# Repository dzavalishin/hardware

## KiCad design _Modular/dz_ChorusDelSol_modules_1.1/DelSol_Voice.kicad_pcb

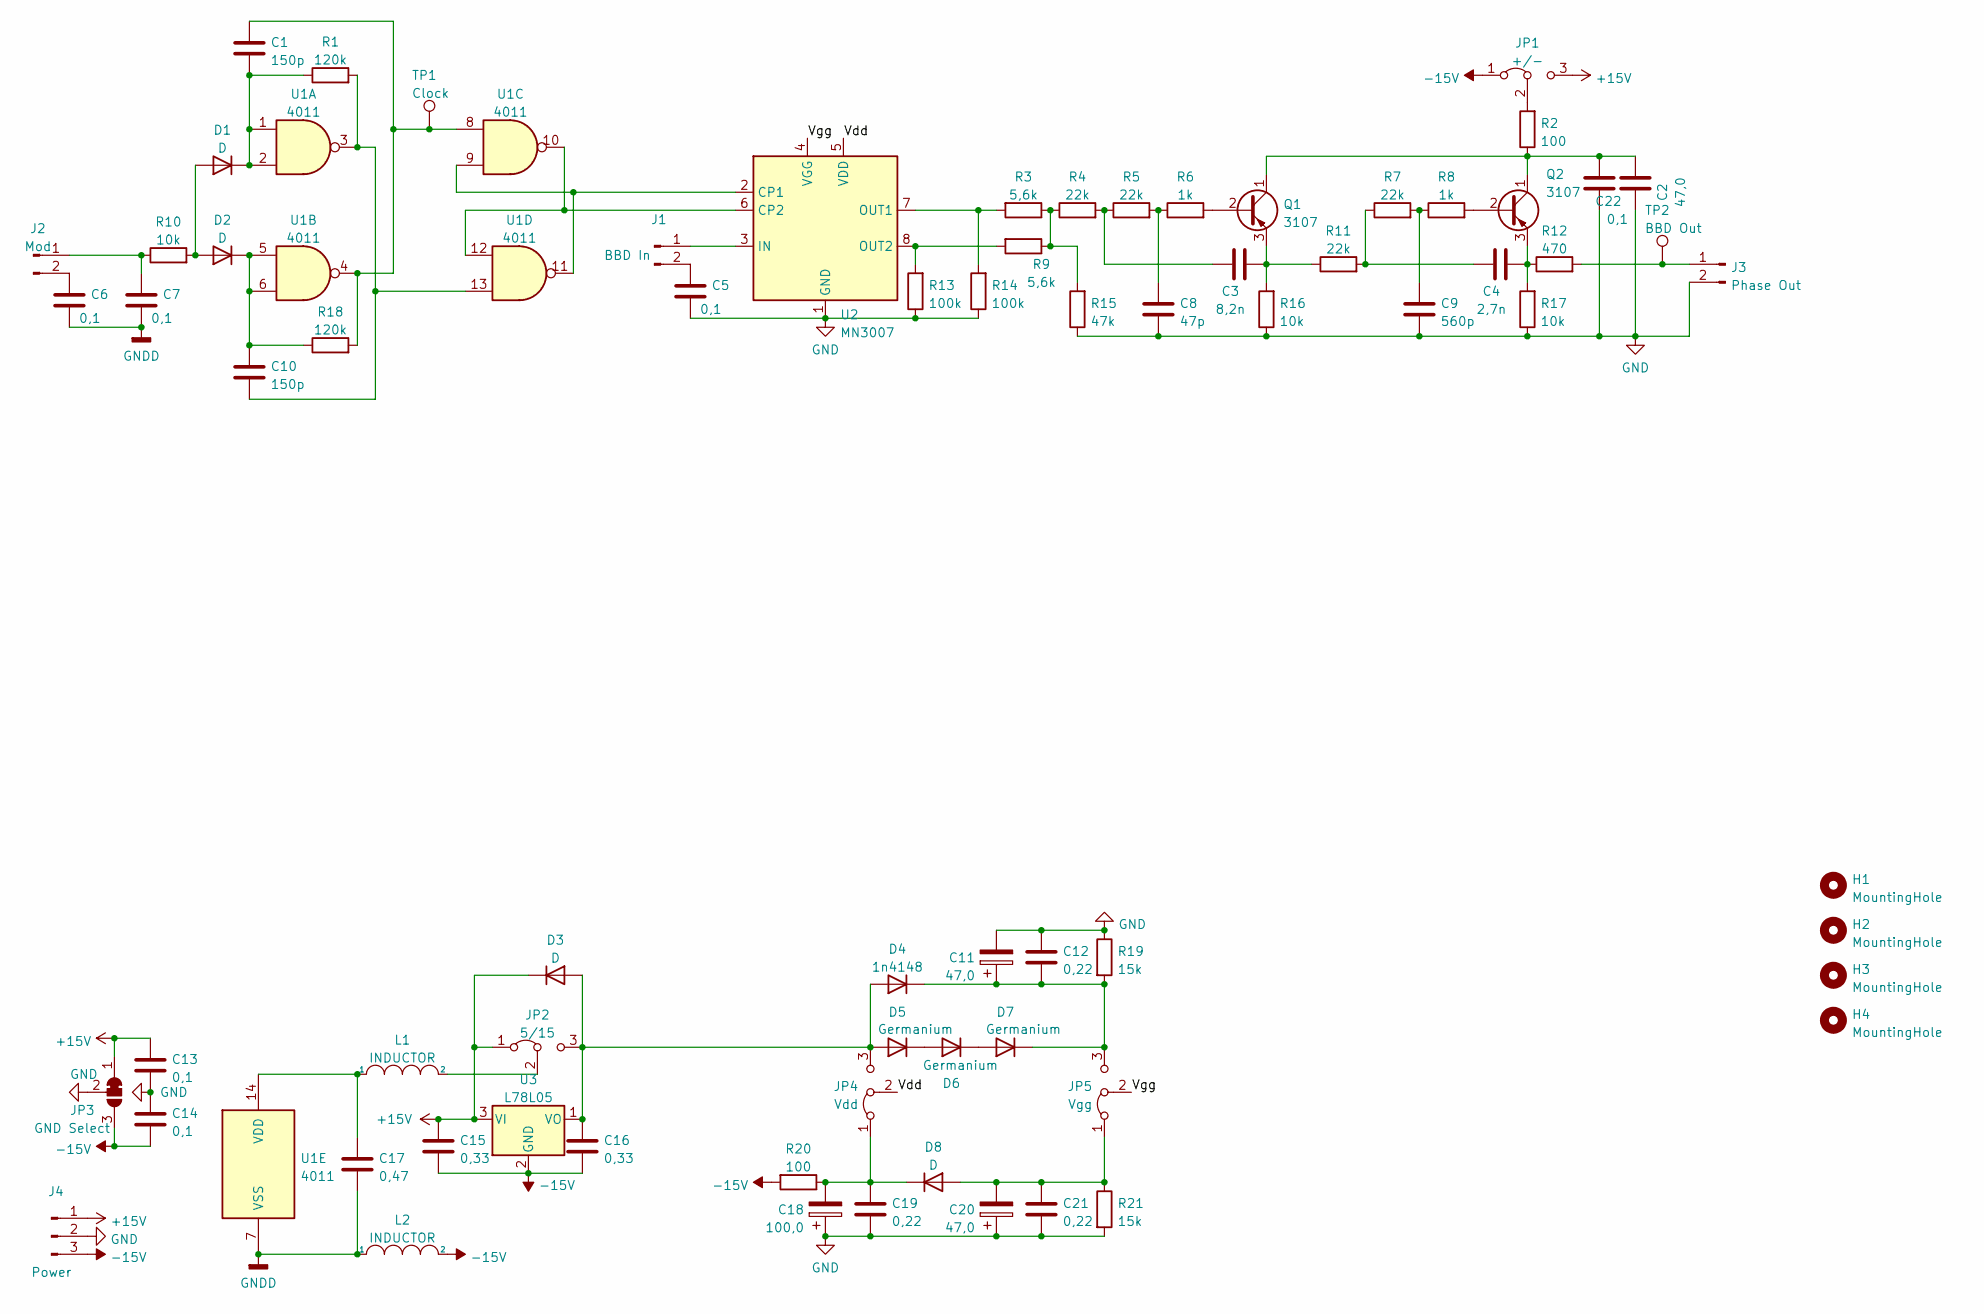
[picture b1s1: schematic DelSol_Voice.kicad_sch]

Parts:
C1, C10: 150p; C_Disc_D5.0mm_W2.5mm_P2.50mm
C2, C11, C20: 47,0; C_Elec_6.3x5.8
C3: 8,2n; C_Disc_D5.0mm_W2.5mm_P2.50mm
C4: 2,7n; C_Disc_D5.0mm_W2.5mm_P2.50mm
C5, C6, C7, C13, C14, C22: 0,1; C_1206_3216Metric_Pad1.33x1.80mm_HandSolder
C8: 47p; C_Disc_D5.0mm_W2.5mm_P2.50mm
C9: 560p; C_Disc_D5.0mm_W2.5mm_P2.50mm
C12, C19, C21: 0,22; C_0805_2012Metric_Pad1.18x1.45mm_HandSolder
C15, C16: 0,33; C_0805_2012Metric_Pad1.18x1.45mm_HandSolder
C17: 0,47; C_0805_2012Metric_Pad1.18x1.45mm_HandSolder
C18: 100,0; C_Elec_6.3x5.8
D1, D2, D3, D8: D; D_MiniMELF_Handsoldering
D4: 1n4148; D_MiniMELF_Handsoldering
D5, D6, D7: Germanium; D_5W_P12.70mm_Horizontal
H1, H2, H3, H4: MountingHole; MountingHole_3.2mm_M3
J1: BBD In; PinHeader_1x02_P2.54mm_Vertical
J2: Mod; PinHeader_1x02_P2.54mm_Vertical
J3: Phase Out; PinHeader_1x02_P2.54mm_Vertical
J4: Power; PinHeader_1x03_P2.54mm_Vertical
JP1: +/-; PinHeader_1x03_P2.54mm_Vertical
JP2: 5/15; PinHeader_1x03_P2.54mm_Vertical
JP3: GND Select; PinHeader_1x03_P2.54mm_Vertical
JP4: Vdd; PinHeader_1x03_P2.54mm_Vertical
JP5: Vgg; PinHeader_1x03_P2.54mm_Vertical
L1, L2: INDUCTOR; L_Radial_D10.0mm_P5.00mm_Fastron_07P
Q1, Q2: 3107; TO-92
R1, R18: 120k; R_1206_3216Metric_Pad1.30x1.75mm_HandSolder
R2, R20: 100; R_1206_3216Metric_Pad1.30x1.75mm_HandSolder
R3, R9: 5,6k; R_1206_3216Metric_Pad1.30x1.75mm_HandSolder
R4, R5, R7, R11: 22k; R_1206_3216Metric_Pad1.30x1.75mm_HandSolder
R6, R8: 1k; R_1206_3216Metric_Pad1.30x1.75mm_HandSolder
R10, R16, R17: 10k; R_1206_3216Metric_Pad1.30x1.75mm_HandSolder
R12: 470; R_1206_3216Metric_Pad1.30x1.75mm_HandSolder
R13, R14: 100k; R_1206_3216Metric_Pad1.30x1.75mm_HandSolder
R15: 47k; R_1206_3216Metric_Pad1.30x1.75mm_HandSolder
R19, R21: 15k; R_1206_3216Metric_Pad1.30x1.75mm_HandSolder
TP1: Clock; PinHeader_1x01_P2.54mm_Vertical
TP2: BBD Out; PinHeader_1x01_P2.54mm_Vertical
U1: 4011; DIP-14_W7.62mm
U2: MN3007; DIP-8_W7.62mm
U3: L78L05; TO-92_Inline

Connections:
+15V: C13.1, C15.1, D3.1 (K), J4.1, JP1.3 (B), JP2.1 (A), JP3.1 (A), U3.3 (VI)
-15V: C14.2, C15.2, C16.2, J4.3, JP1.1 (A), JP3.3 (B), L2.2, R20.2, U3.2 (GND)
/Vdd: JP4.2 (C), U2.5 (VDD)
/Vgg: JP5.2 (C), U2.4 (VGG)
GND: C2.1, C5.2, C8.1, C9.1, C11.2, C12.1, C13.2, C14.1, C18.1, C19.2, C20.1, C21.2, C22.1, J3.2, J4.2, JP3.2 (C), R13.1, R14.1, R15.1, R16.1, R17.1, R19.1, R21.2, U2.1 (GND)
GNDD: C6.2, C7.2, C17.2, L2.1, U1.7 (VSS)
unnamed: C1.2, D1.1 (K), R1.1, U1.1, U1.2
unnamed: C2.2, C22.2, Q1.1 (C), Q2.1 (C), R2.1
unnamed: C3.1, R4.2, R5.1
unnamed: C3.2, Q1.3 (E), R11.1, R16.2
unnamed: C4.1, R7.1, R11.2
unnamed: C4.2, Q2.3 (E), R12.1, R17.2
unnamed: C5.1, J1.2
unnamed: C6.1, J2.2
unnamed: C7.1, J2.1, R10.1
unnamed: C8.2, R5.2, R6.1
unnamed: C9.2, R7.2, R8.1
unnamed: C10.1, D2.1 (K), R18.1, U1.5, U1.6
unnamed: C10.2, R1.2, U1.3, U1.13
unnamed: C11.1, C12.2, D4.1 (K), D7.1 (K), JP5.3 (B), R19.2
unnamed: C16.1, D3.2 (A), D4.2 (A), D5.2 (A), JP2.3 (B), JP4.3 (B), U3.1 (VO)
unnamed: C17.1, L1.1, U1.14 (VDD)
unnamed: C18.2, C19.1, D8.1 (K), JP4.1 (A), R20.1
unnamed: C20.2, C21.1, D8.2 (A), JP5.1 (A), R21.1
unnamed: D1.2 (A), D2.2 (A), R10.2
unnamed: D5.1 (K), D6.2 (A)
unnamed: D6.1 (K), D7.2 (A)
unnamed: J1.1, U2.3 (IN)
unnamed: J3.1, R12.2, TP2.1
unnamed: JP1.2 (C), R2.2
unnamed: JP2.2 (C), L1.2
unnamed: Q1.2 (B), R6.2
unnamed: Q2.2 (B), R8.2
unnamed: R9.2, R13.2, U2.8 (OUT2)
unnamed: R3.2, R14.2, U2.7 (OUT1)
unnamed: R3.1, R4.1, R9.1, R15.2
unnamed: C1.1, R18.2, TP1.1, U1.4, U1.8
unnamed: U1.10, U1.12, U2.6 (CP2)
unnamed: U1.9, U1.11, U2.2 (CP1)

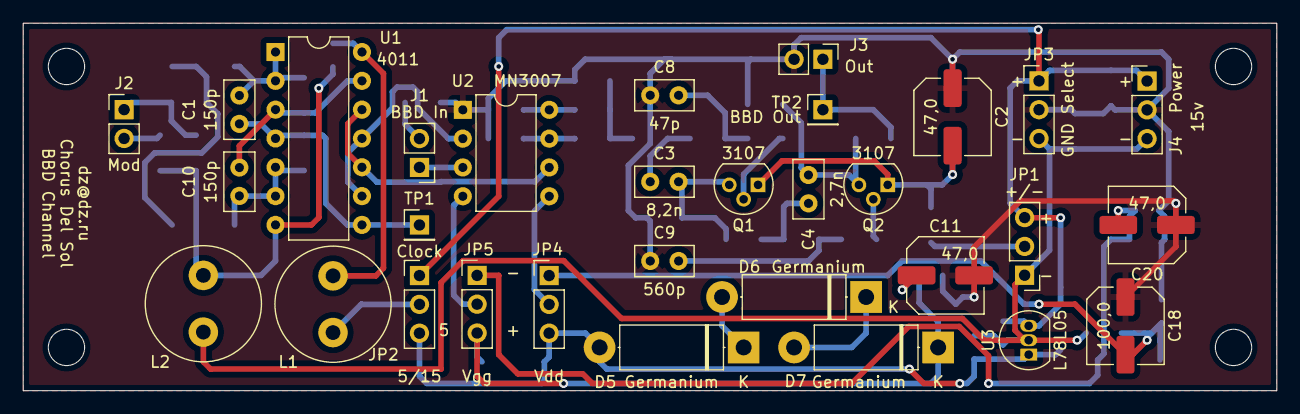
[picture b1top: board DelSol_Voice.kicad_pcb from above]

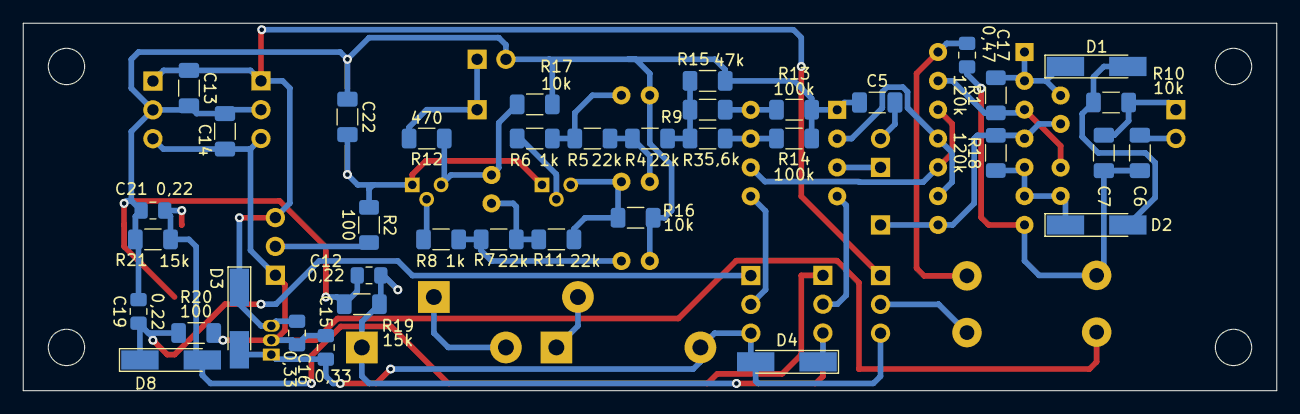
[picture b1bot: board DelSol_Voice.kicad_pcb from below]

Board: 2 copper layers, 110.5 x 32.4 mm, 73 parts (38 on the bottom side), 39 nets.

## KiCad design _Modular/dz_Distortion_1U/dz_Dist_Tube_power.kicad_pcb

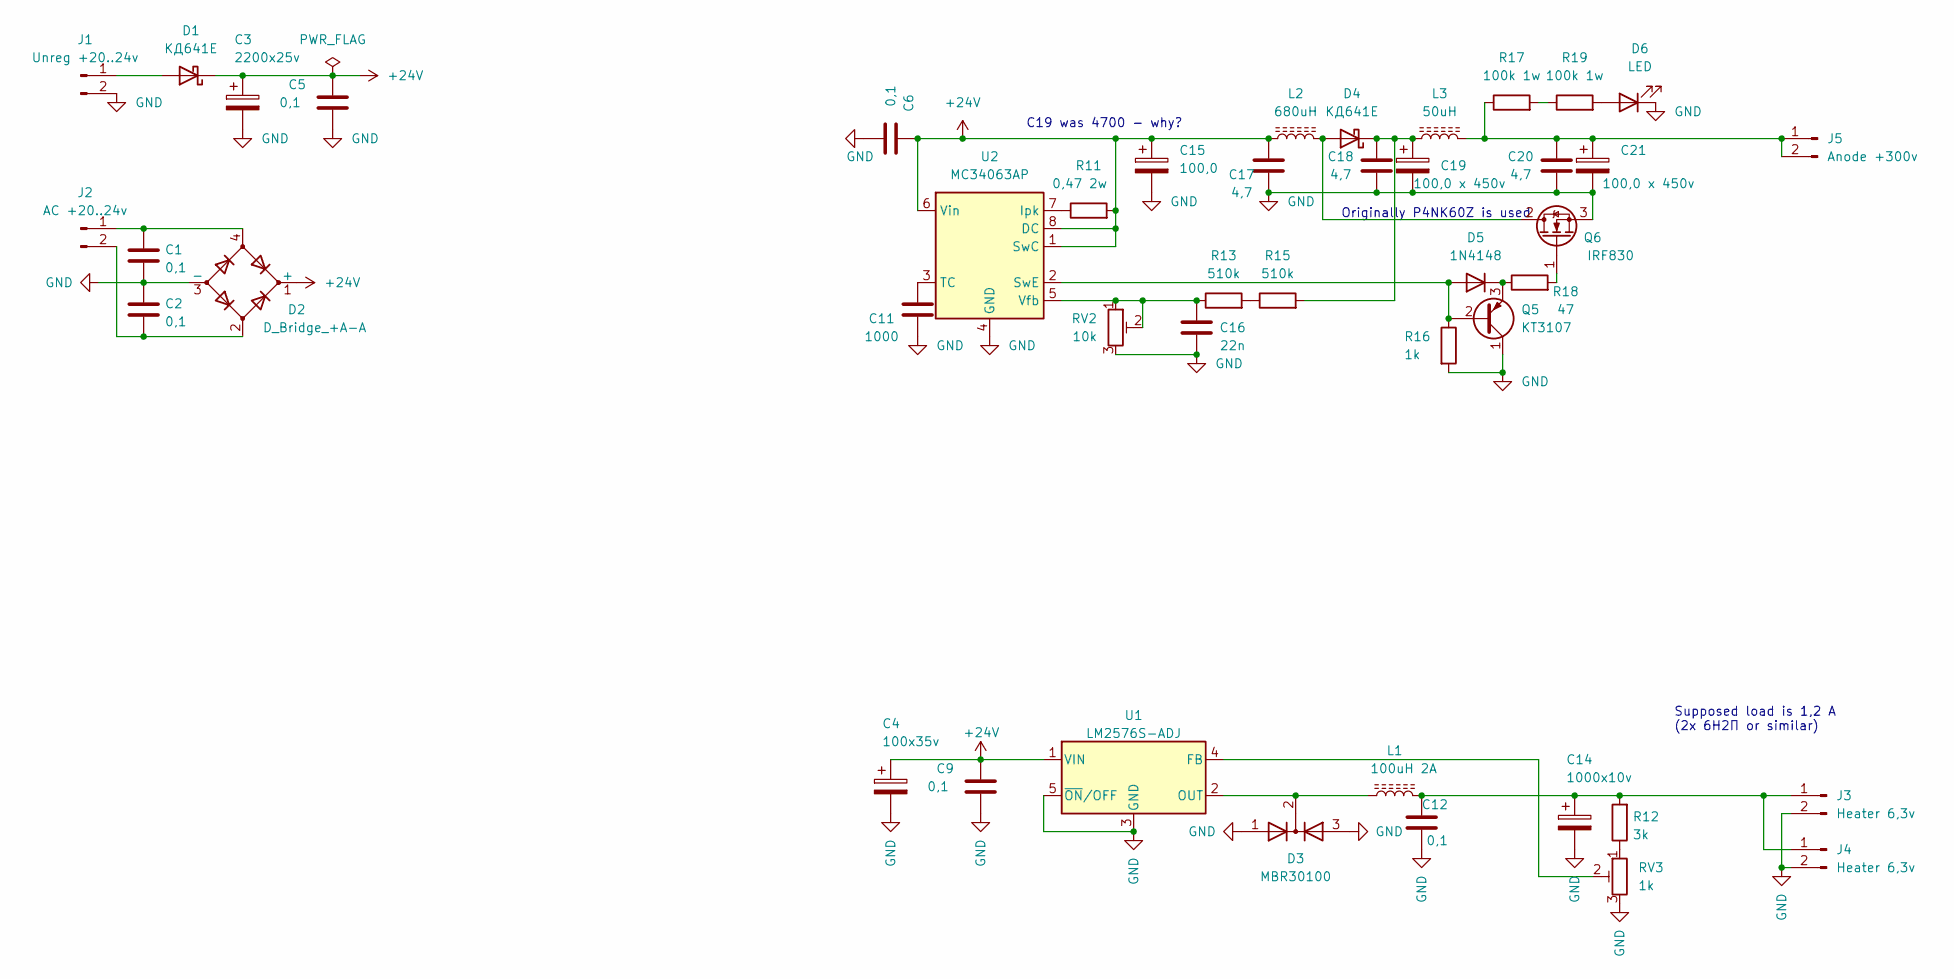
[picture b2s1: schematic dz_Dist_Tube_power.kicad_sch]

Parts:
C1, C2: 0,1; C_Rect_L13.0mm_W6.0mm_P10.00mm_FKS3_FKP3_MKS4
C3: 2200x25v; CP_Radial_D13.0mm_P5.00mm
C4: 100x35v; CP_Radial_D10.0mm_P5.00mm
C5, C6, C9, C12: 0,1; C_1206_3216Metric_Pad1.33x1.80mm_HandSolder
C11: 1000; C_0805_2012Metric_Pad1.18x1.45mm_HandSolder
C14: 1000x10v; CP_Radial_D13.0mm_P5.00mm
C15: 100,0; CP_Radial_D10.0mm_P2.50mm_P5.00mm
C16: 22n; C_0805_2012Metric_Pad1.18x1.45mm_HandSolder
C17, C18, C20: 4,7; C_0805_2012Metric_Pad1.18x1.45mm_HandSolder
C19, C21: 100,0 x 450v; CP_Radial_D22.0mm_P10.00mm_SnapIn
D1, D4: КД641Е; TO-220-2_Vertical
D2: D_Bridge_+A-A; Diode_Bridge_Round_D9.0mm
D3: MBR30100; TO-220-3_Vertical
D5: 1N4148; D_DO-35_SOD27_P2.54mm_Vertical_KathodeUp
D6: LED; LED_1206_3216Metric_Pad1.42x1.75mm_HandSolder
J1: Unreg +20..24v; PinHeader_1x02_P2.54mm_Vertical
J2: AC +20..24v; PinHeader_1x02_P2.54mm_Vertical
J3, J4: Heater 6,3v; PinHeader_1x02_P2.54mm_Vertical
J5: Anode +300v; PinHeader_1x02_P2.54mm_Vertical
L1: 100uH 2A; L_Toroid_Vertical_L14.7mm_W8.6mm_P5.58mm_Pulse_KM-1
L2: 680uH; L_Radial_D10.0mm_P5.00mm_Fastron_07M
L3: 50uH; L_Radial_D10.0mm_P5.00mm_Fastron_07M
Q5: KT3107; TO-92
Q6: IRF830; TO-220-3_Vertical
R11: 0,47 2w; R_Axial_DIN0411_L9.9mm_D3.6mm_P5.08mm_Vertical
R12: 3k; R_1206_3216Metric_Pad1.30x1.75mm_HandSolder
R13, R15: 510k; R_Axial_DIN0309_L9.0mm_D3.2mm_P12.70mm_Horizontal
R16: 1k; R_1206_3216Metric_Pad1.30x1.75mm_HandSolder
R17, R19: 100k 1w; R_Axial_DIN0309_L9.0mm_D3.2mm_P12.70mm_Horizontal
R18: 47; R_Axial_DIN0414_L11.9mm_D4.5mm_P5.08mm_Vertical
RV2: 10k; Potentiometer_Runtron_RM-065_Vertical
RV3: 1k; Potentiometer_Runtron_RM-065_Vertical
U1: LM2576S-ADJ; TO-263-5_TabPin3
U2: MC34063AP; DIP-8_W7.62mm

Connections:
+24V: C3.1, C4.1, C5.1, C6.1, C9.1, C15.1, C17.2, D1.1 (K), D2.1 (+), L2.1, R11.2, U1.1 (VIN), U2.1 (SwC), U2.6 (Vin), U2.8 (DC)
GND: C1.2, C2.1, C3.2, C4.2, C5.2, C6.2, C9.2, C11.1, C12.1, C14.2, C15.2, C16.1, C17.1, C18.1, C19.2, C20.1, C21.2, D2.3 (-), D3.1 (A), D3.3 (A), D6.1 (K), J1.2, J3.2, J4.2, Q5.1 (C), Q6.3 (S), R16.2, RV2.3, RV3.3, U1.3 (GND), U1.5 (~ON/OFF), U2.4 (GND)
unnamed: C1.1, D2.4, J2.1
unnamed: C2.2, D2.2, J2.2
unnamed: C11.2, U2.3 (TC)
unnamed: C12.2, C14.1, J3.1, J4.1, L1.2, R12.2
unnamed: C16.2, R13.1, RV2.1, RV2.2, U2.5 (Vfb)
unnamed: C18.2, C19.1, D4.1 (K), L3.1, R15.2
unnamed: C20.2, C21.1, J5.1, J5.2, L3.2, R17.1
unnamed: D1.2 (A), J1.1
unnamed: D3.2 (K), L1.1, U1.2 (OUT)
unnamed: D4.2 (A), L2.2, Q6.2 (D)
unnamed: D5.1 (K), Q5.3 (E), R18.1
unnamed: D5.2 (A), Q5.2 (B), R16.1, U2.2 (SwE)
unnamed: D6.2 (A), R19.2
unnamed: Q6.1 (G), R18.2
unnamed: R11.1, U2.7 (Ipk)
unnamed: R12.1, RV3.1
unnamed: R13.2, R15.1
unnamed: R17.2, R19.1
unnamed: RV3.2, U1.4 (FB)

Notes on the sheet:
C19 was 4700 - why?
Originally P4NK60Z is used
Supposed load is 1,2 A (2x 6Н2П or similar)

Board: 2 copper layers, 45 parts (10 on the bottom side), 21 nets, no tracks yet.

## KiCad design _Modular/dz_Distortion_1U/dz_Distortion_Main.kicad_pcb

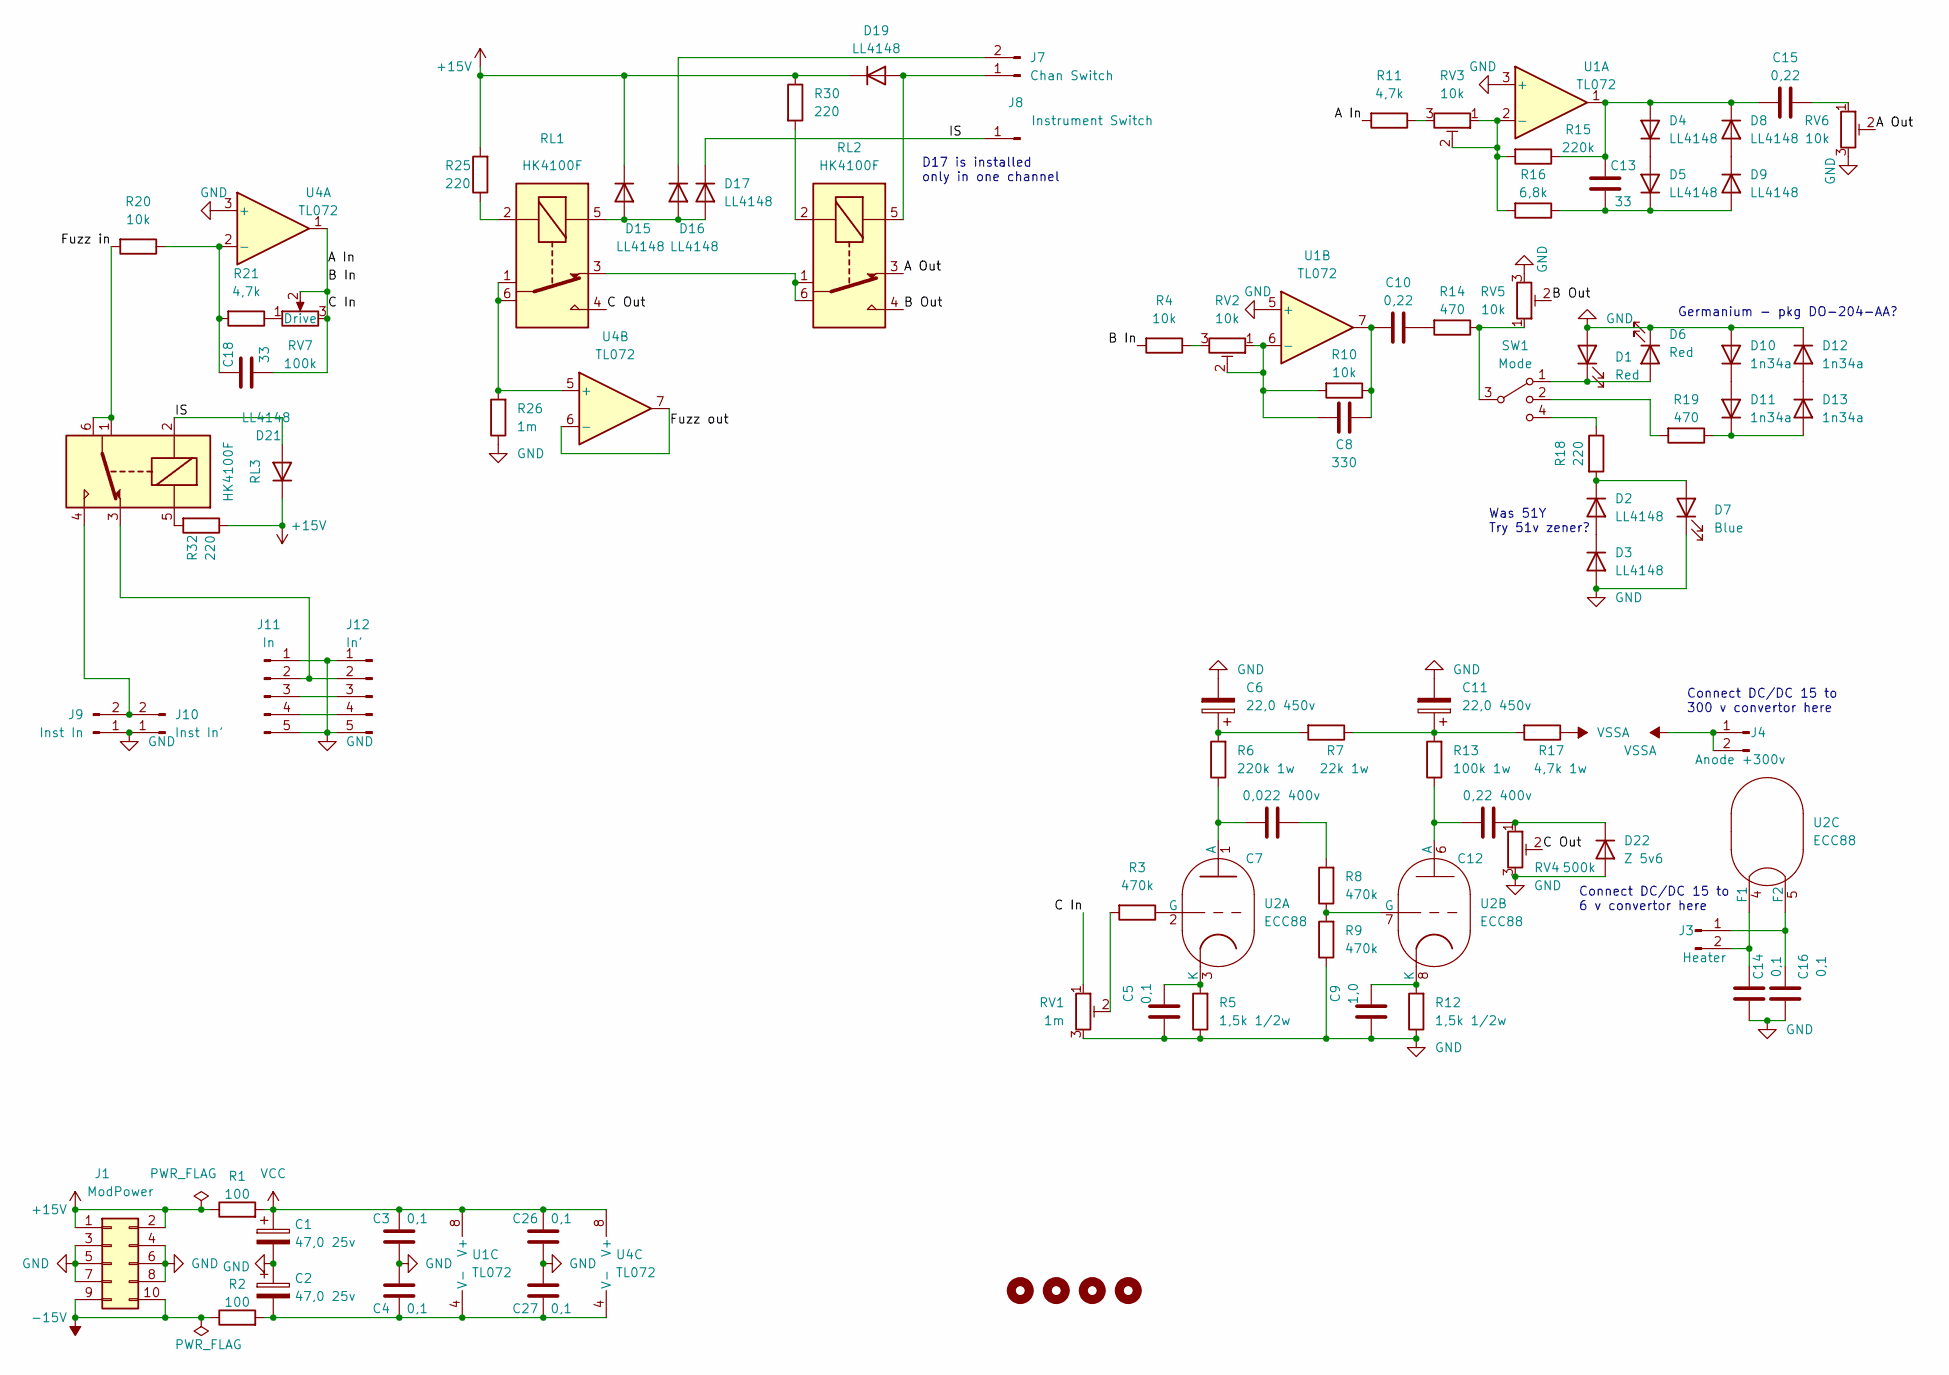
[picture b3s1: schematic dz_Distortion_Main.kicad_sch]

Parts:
C1, C2: 47,0 25v; CP_Radial_D5.0mm_P2.50mm
C3, C4, C5, C14, C16, C26, C27: 0,1; C_1206_3216Metric_Pad1.33x1.80mm_HandSolder
C6, C11: 22,0 450v; CP_Radial_D13.0mm_P5.00mm
C7: 0,022 400v; C_Rect_L7.0mm_W3.5mm_P5.00mm
C8: 330; C_Disc_D5.0mm_W2.5mm_P2.50mm
C9: 1,0; C_0805_2012Metric_Pad1.18x1.45mm_HandSolder
C10, C15: 0,22; C_0805_2012Metric_Pad1.18x1.45mm_HandSolder
C12: 0,22 400v; C_Rect_L7.0mm_W3.5mm_P5.00mm
C13, C18: 33; C_Disc_D5.0mm_W2.5mm_P2.50mm
D1, D6: Red; LED_1206_3216Metric_Pad1.42x1.75mm_HandSolder
D2, D3, D4, D5, D8, D9, D15, D16, D17, D19, D21: LL4148; D_MiniMELF
D7: Blue; LED_D3.0mm
D10, D11, D12, D13: 1n34a; D_DO-34_SOD68_P2.54mm_Vertical_KathodeUp
D22: Z 5v6; D_MiniMELF
H1, H2, H3, H4: MountingHole; MountingHole_3.2mm_M3
J1: ModPower; PinHeader_2x05_P2.54mm_Vertical
J3: Heater; PinHeader_1x02_P2.54mm_Vertical
J4: Anode +300v; PinHeader_1x02_P2.54mm_Vertical
J7: Chan Switch; PinHeader_1x02_P2.54mm_Vertical
J8: Instrument Switch; PinHeader_1x01_P2.54mm_Vertical
J9: Inst In; PinHeader_1x02_P2.54mm_Vertical
J10: Inst In'; PinHeader_1x02_P2.54mm_Vertical
J11: In; PinHeader_1x05_P2.54mm_Vertical
J12: In'; PinHeader_1x05_P2.54mm_Vertical
R1, R2: 100; R_1206_3216Metric_Pad1.30x1.75mm_HandSolder
R3, R9: 470k; R_Axial_DIN0309_L9.0mm_D3.2mm_P5.08mm_Vertical
R4, R10, R20: 10k; R_1206_3216Metric_Pad1.30x1.75mm_HandSolder
R5, R12: 1,5k 1/2w; R_Axial_DIN0309_L9.0mm_D3.2mm_P5.08mm_Vertical
R6: 220k 1w; R_Axial_DIN0309_L9.0mm_D3.2mm_P12.70mm_Horizontal
R7: 22k 1w; R_Axial_DIN0309_L9.0mm_D3.2mm_P12.70mm_Horizontal
R8: 470k; R_Axial_DIN0309_L9.0mm_D3.2mm_P12.70mm_Horizontal
R11, R21: 4,7k; R_1206_3216Metric_Pad1.30x1.75mm_HandSolder
R13: 100k 1w; R_Axial_DIN0309_L9.0mm_D3.2mm_P12.70mm_Horizontal
R14, R19: 470; R_1206_3216Metric_Pad1.30x1.75mm_HandSolder
R15: 220k; R_1206_3216Metric_Pad1.30x1.75mm_HandSolder
R16: 6,8k; R_1206_3216Metric_Pad1.30x1.75mm_HandSolder
R17: 4,7k 1w; R_Axial_DIN0309_L9.0mm_D3.2mm_P12.70mm_Horizontal
R18, R25, R30, R32: 220; R_1206_3216Metric_Pad1.30x1.75mm_HandSolder
R26: 1m; R_1206_3216Metric_Pad1.30x1.75mm_HandSolder
RL1, RL2, RL3: HK4100F
RV1: 1m; Potentiometer_Runtron_RM-065_Vertical
RV2, RV3, RV5, RV6: 10k; Potentiometer_Runtron_RM-065_Vertical
RV4: 500k; Potentiometer_Runtron_RM-065_Vertical
RV7: 100k; PinHeader_1x03_P2.54mm_Vertical
SW1: Mode; PinHeader_1x04_P2.54mm_Vertical
U1: TL072; DIP-8_W7.62mm_LongPads
U2: ECC88; Valve_ECC-83-2
U4: TL072; DIP-8_W7.62mm

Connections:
+15V: D15.1 (K), D19.1 (K), D21.1 (K), J1.1, J1.2, R1.1, R25.2, R30.1, R32.1
-15V: J1.9, J1.10, R2.1
/A In: C18.2, R4.2, R11.2, RV1.1, RV7.2, RV7.3, U4.1
/A Out: RL2.3, RV6.2
/B Out: RL2.4, RV5.2
/C Out: RL1.4, RV4.2
/Fuzz in: R20.2, RL3.1, RL3.6
/Fuzz out: U4.6 (-), U4.7
/IS: D17.1 (K), D21.2 (A), J8.1, RL3.2
GND: C1.2, C2.1, C3.1, C4.2, C5.1, C6.2, C9.1, C11.2, C14.1, C16.1, C26.1, C27.2, D1.2 (A), D3.2 (A), D6.1 (K), D7.1 (K), D10.2 (A), D12.1 (K), D22.2 (A), J1.3, J1.4, J1.5, J1.6, J1.7, J1.8, J9.1, J10.1, J11.1, J11.5, J12.1, J12.5, R5.1, R9.1, R12.1, R26.1, RV1.3, RV4.3, RV5.3, RV6.3, U1.3 (+), U1.5 (+), U4.3 (+)
unnamed: C2.2, C4.1, C27.1, R2.2, U1.4 (V-), U4.4 (V-)
unnamed: C5.2, R5.2, U2.3 (K)
unnamed: C6.1, R6.2, R7.2
unnamed: C7.1, R8.2
unnamed: C7.2, R6.1, U2.1 (A)
unnamed: C8.2, R10.2, RV2.1, RV2.2, U1.6 (-)
unnamed: C9.2, R12.2, U2.8 (K)
unnamed: C8.1, C10.1, R10.1, U1.7
unnamed: C10.2, R14.2
unnamed: C11.1, R7.1, R13.2, R17.2
unnamed: C12.1, D22.1 (K), RV4.1
unnamed: C12.2, R13.1, U2.6 (A)
unnamed: C13.1, C15.1, D4.2 (A), D8.1 (K), R15.1, U1.1
unnamed: C13.2, D5.1 (K), D9.2 (A), R16.1
unnamed: C14.2, J3.2, U2.4 (F1)
unnamed: C15.2, RV6.1
unnamed: C16.2, J3.1, U2.5 (F2)
unnamed: C18.1, R20.1, R21.2, U4.2 (-)
unnamed: D1.1 (K), D6.2 (A), SW1.1
unnamed: D2.1 (K), D7.2 (A), R18.2
unnamed: D2.2 (A), D3.1 (K)
unnamed: D4.1 (K), D5.2 (A)
unnamed: D8.2 (A), D9.1 (K)
unnamed: D10.1 (K), D11.2 (A)
unnamed: D11.1 (K), D13.2 (A), R19.1
unnamed: D12.2 (A), D13.1 (K)
unnamed: D15.2 (A), D16.2 (A), D17.2 (A), RL1.5
unnamed: D16.1 (K), J7.2
unnamed: D19.2 (A), J7.1, RL2.5
unnamed: J9.2, J10.2, RL3.4
unnamed: J11.2, J12.2, RL3.3
unnamed: J11.3, J12.3
unnamed: J11.4, J12.4
unnamed: R3.1, U2.2 (G)
unnamed: R3.2, RV1.2
unnamed: R4.1, RV2.3
unnamed: R8.1, R9.2, U2.7 (G)
unnamed: R11.1, RV3.3
unnamed: R14.1, RV5.1, SW1.3
unnamed: R15.2, R16.2, RV3.1, RV3.2, U1.2 (-)
unnamed: R18.1, SW1.4
unnamed: R19.2, SW1.2
unnamed: R21.1, RV7.1
unnamed: R25.1, RL1.2
unnamed: R26.2, RL1.1, RL1.6, U4.5 (+)
unnamed: R30.2, RL2.2
unnamed: R32.2, RL3.5
unnamed: RL1.3, RL2.1, RL2.6
VCC: C1.1, C3.2, C26.2, R1.2, U1.8 (V+), U4.8 (V+)
VSSA: J4.1, J4.2, R17.1

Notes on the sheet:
Connect DC/DC 15 to 6 v convertor here
Was 51Y Try 51v zener?
Connect DC/DC 15 to 300 v convertor here
Germanium - pkg DO-204-AA?
D17 is installed only in one channel

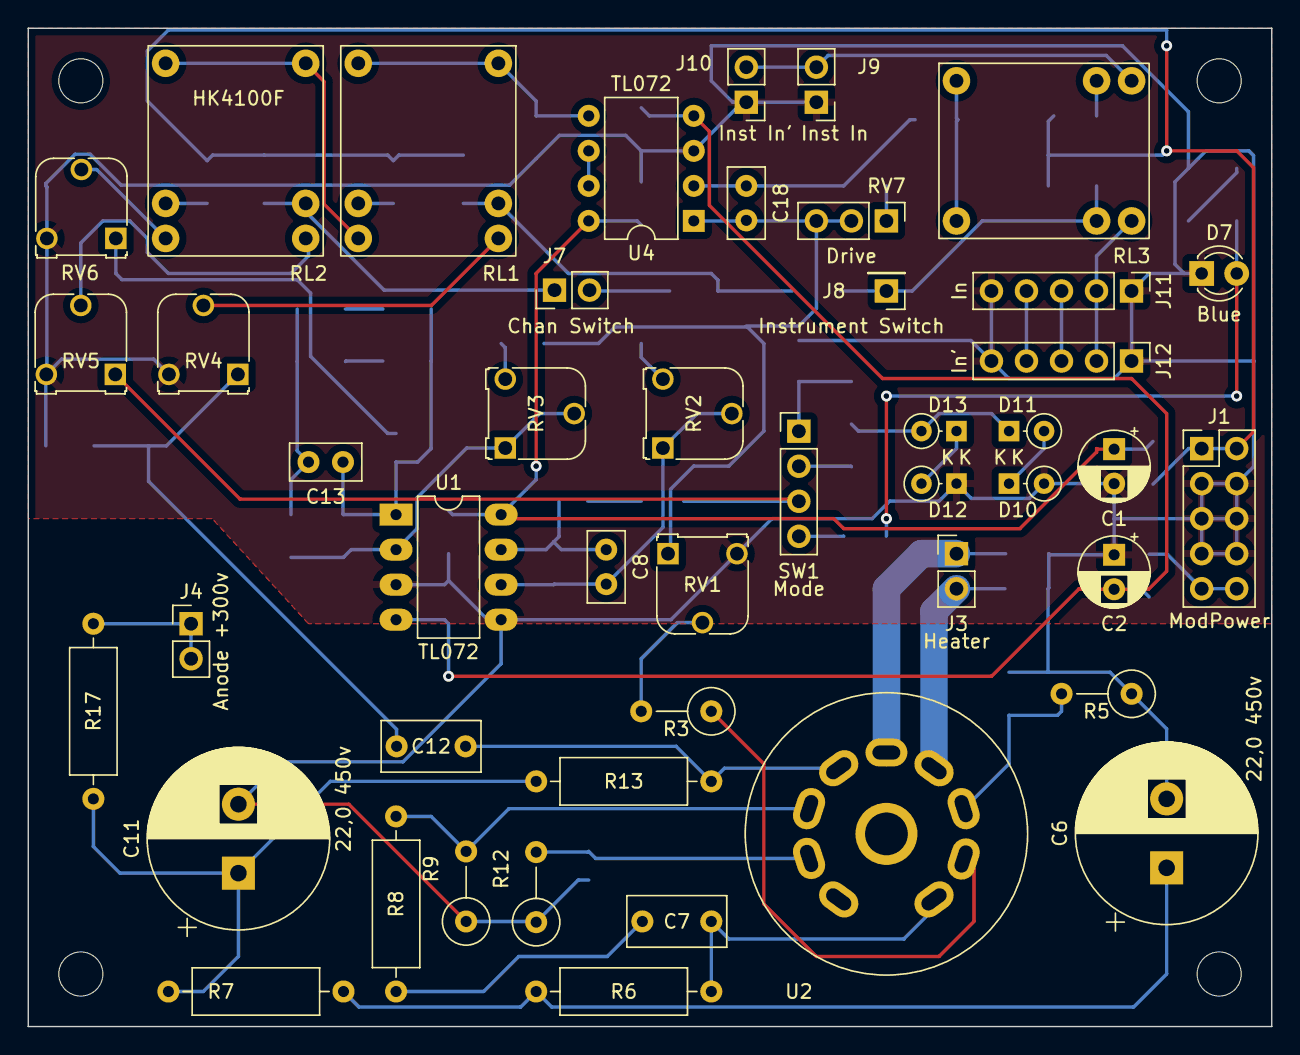
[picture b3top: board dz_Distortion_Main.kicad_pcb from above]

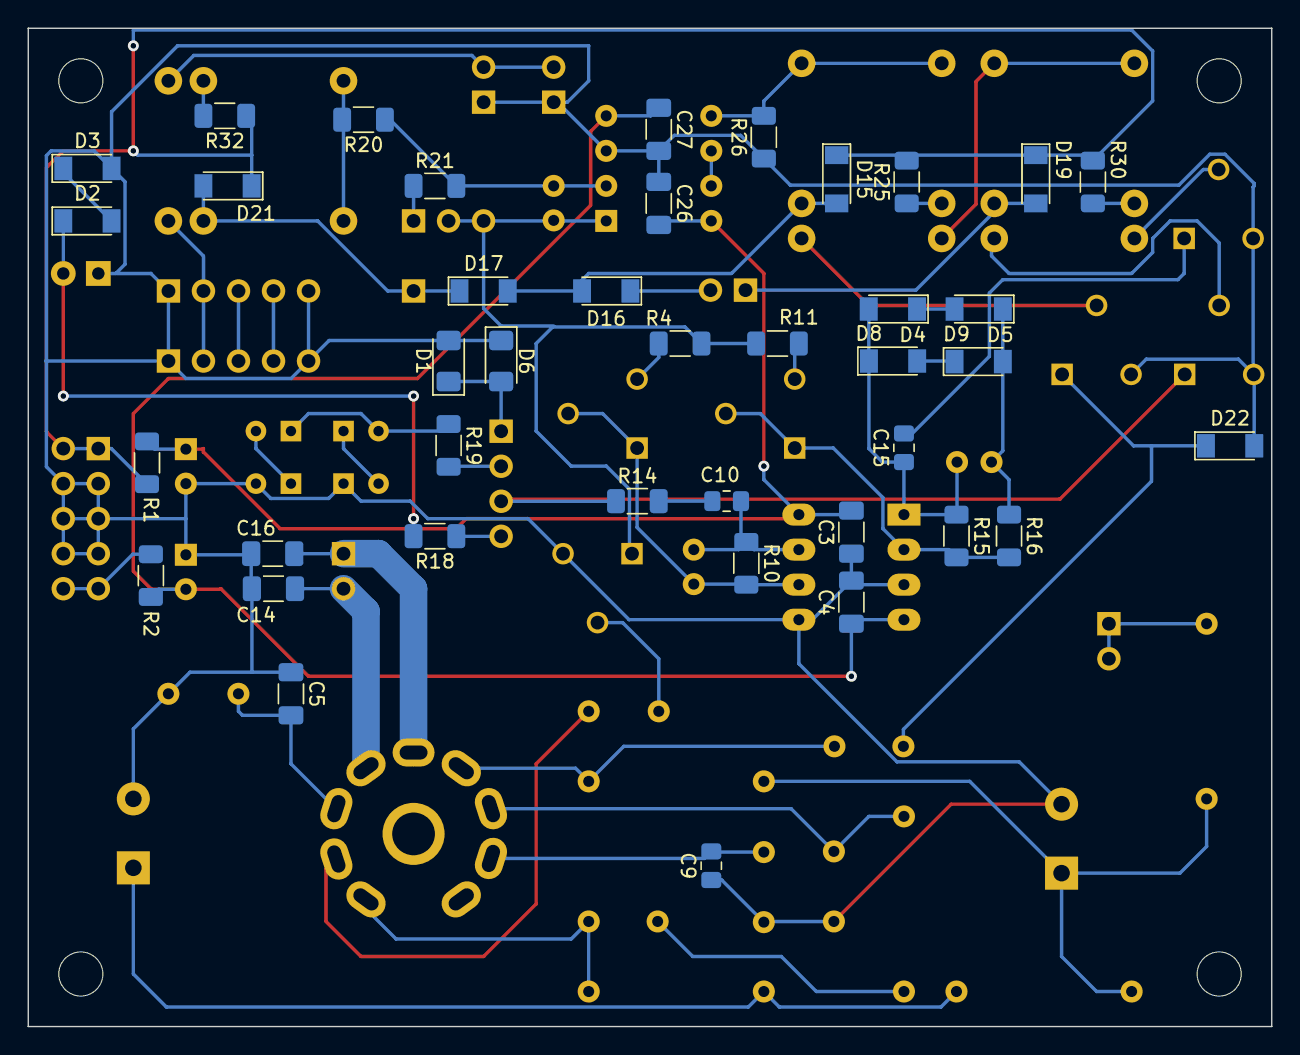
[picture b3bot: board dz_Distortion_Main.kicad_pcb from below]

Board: 2 copper layers, 90.2 x 72.4 mm, 90 parts (40 on the bottom side), 60 nets.

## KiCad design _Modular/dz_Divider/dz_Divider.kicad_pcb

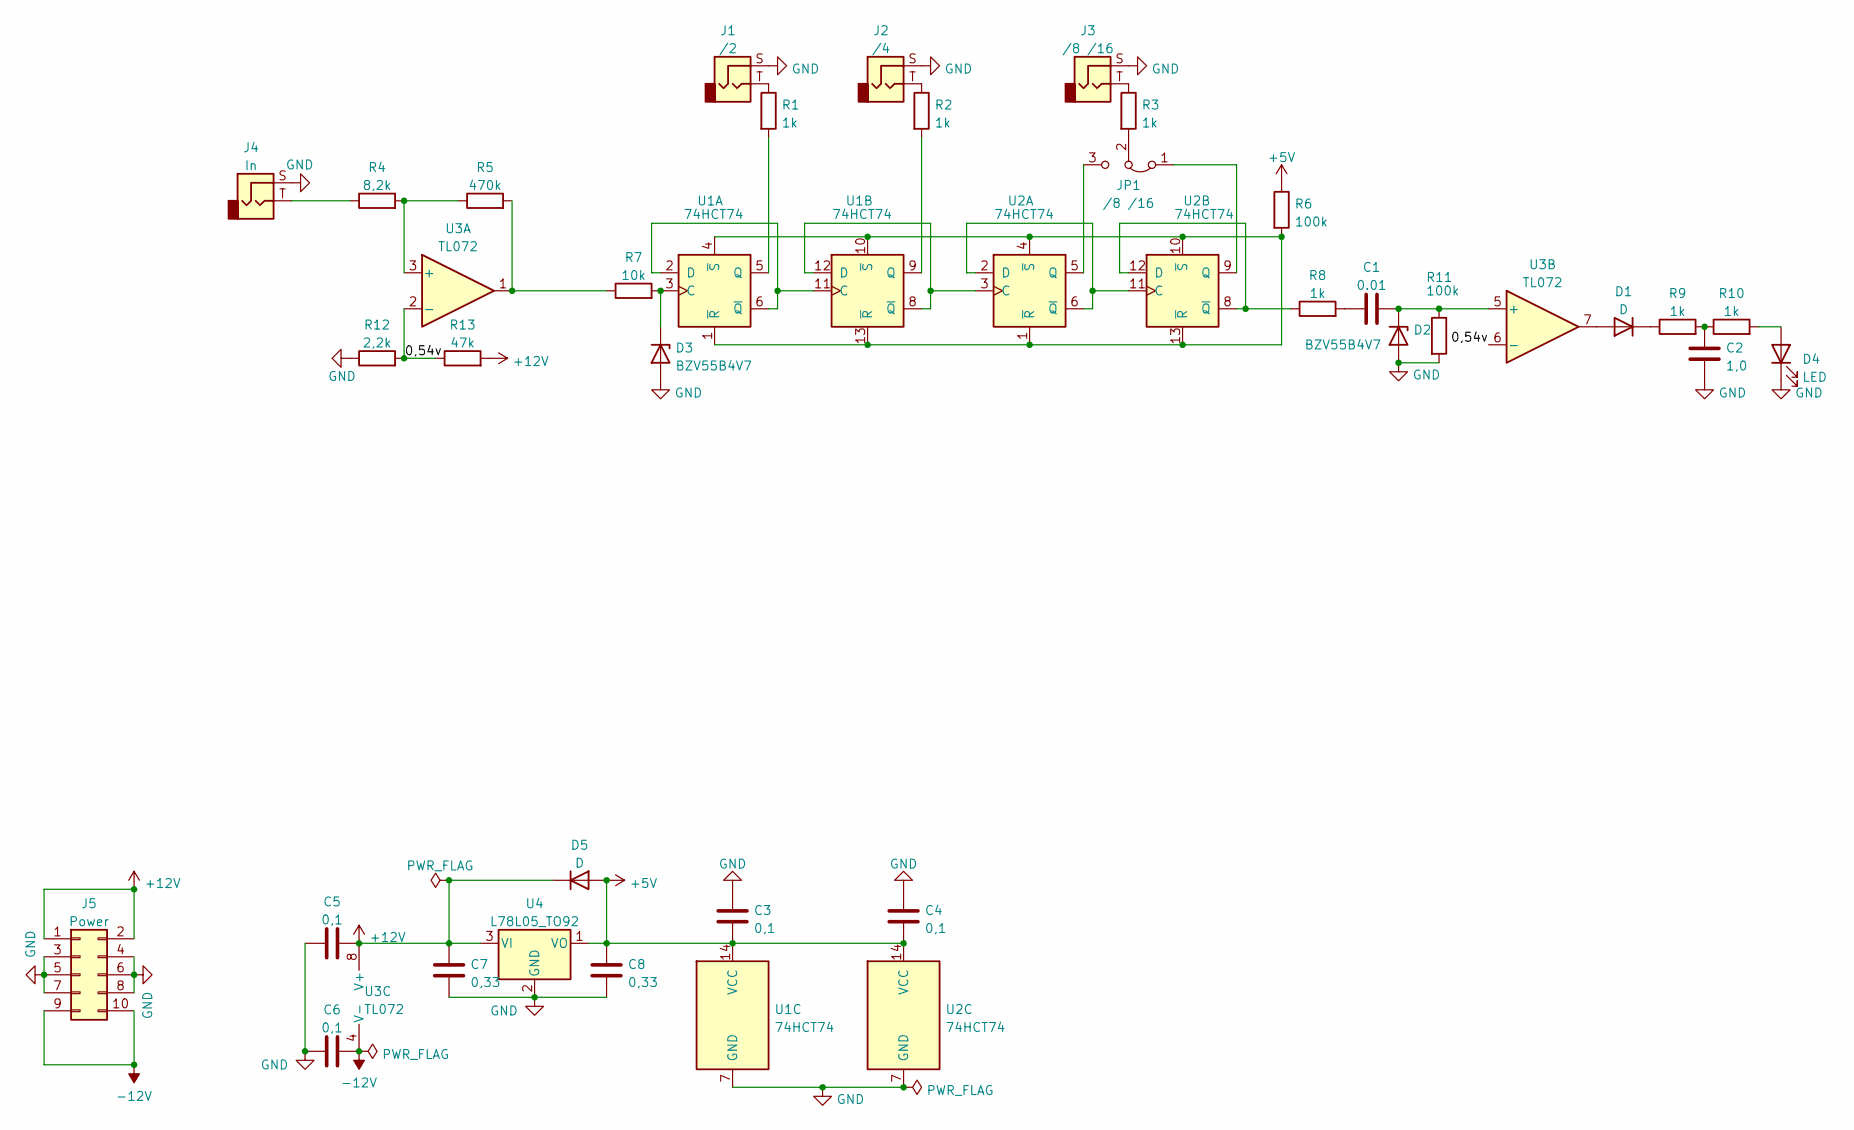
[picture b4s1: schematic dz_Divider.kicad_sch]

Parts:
C1: 0.01; C_Disc_D5.0mm_W2.5mm_P5.00mm
C2: 1,0; C_Disc_D5.0mm_W2.5mm_P5.00mm
C3, C4, C5, C6: 0,1; C_1206_3216Metric_Pad1.33x1.80mm_HandSolder
C7, C8: 0,33; C_Disc_D5.0mm_W2.5mm_P5.00mm
D1, D5: D; D_MiniMELF_Handsoldering
D2, D3: BZV55B4V7; D_MiniMELF_Handsoldering
D4: LED; LED_D3.0mm_Horizontal_O1.27mm_Z2.0mm
J1: /2; Jack_3.5mm_CUI_SJ1-3525N_Horizontal
J2: /4; Jack_3.5mm_CUI_SJ1-3525N_Horizontal
J3: /8 /16; Jack_3.5mm_CUI_SJ1-3525N_Horizontal
J4: In; Jack_3.5mm_CUI_SJ1-3525N_Horizontal
J5: Power; PinHeader_2x05_P2.54mm_Vertical
JP1: /8 /16; PinHeader_1x03_P2.54mm_Vertical
R1, R2, R3, R8, R9, R10: 1k; R_1206_3216Metric_Pad1.30x1.75mm_HandSolder
R4: 8,2k; R_1206_3216Metric_Pad1.30x1.75mm_HandSolder
R5: 470k; R_1206_3216Metric_Pad1.30x1.75mm_HandSolder
R6, R11: 100k; R_1206_3216Metric_Pad1.30x1.75mm_HandSolder
R7: 10k; R_1206_3216Metric_Pad1.30x1.75mm_HandSolder
R12: 2,2k; R_1206_3216Metric_Pad1.30x1.75mm_HandSolder
R13: 47k; R_1206_3216Metric_Pad1.30x1.75mm_HandSolder
U1, U2: 74HCT74; DIP-14_W7.62mm_Socket_LongPads
U3: TL072; DIP-8_W7.62mm_Socket_LongPads
U4: L78L05_TO92; TO-92_Inline

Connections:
+5V: C3.2, C4.2, C8.2, D5.2 (A), R6.1, U1.14 (VCC), U2.14 (VCC), U4.1 (VO)
+12V: C5.2, C7.2, D5.1 (K), J5.1, J5.2, R13.2, U3.8 (V+), U4.3 (VI)
-12V: C6.2, J5.9, J5.10, U3.4 (V-)
/0,54v: R12.2, R13.1, U3.2 (-), U3.6 (-)
GND: C2.1, C3.1, C4.1, C5.1, C6.1, C7.1, C8.1, D2.2 (A), D3.2 (A), D4.1 (K), J1.S, J2.S, J3.S, J4.S, J5.3, J5.4, J5.5, J5.6, J5.7, J5.8, R11.2, R12.1, U1.7 (GND), U2.7 (GND), U4.2 (GND)
unnamed: C1.1, R8.2
unnamed: C2.2, R9.2, R10.1
unnamed: D1.1 (K), R9.1
unnamed: D4.2 (A), R10.2
unnamed: J1.T, R1.1
unnamed: J2.T, R2.1
unnamed: J3.T, R3.1
unnamed: J4.T, R4.1
unnamed: JP1.2 (C), R3.2
unnamed: R6.2, U1.1 (~R), U1.4 (~S), U1.10 (~S), U1.13 (~R), U2.1 (~R), U2.4 (~S), U2.10 (~S), U2.13 (~R)
unnamed: D3.1 (K), R7.2, U1.3 (C)
unnamed: R1.2, U1.5 (Q)
unnamed: U1.2 (D), U1.6 (~Q), U1.11 (C)
unnamed: R2.2, U1.9 (Q)
unnamed: U1.8 (~Q), U1.12 (D), U2.3 (C)
unnamed: U2.2 (D), U2.6 (~Q), U2.11 (C)
unnamed: JP1.3 (B), U2.5 (Q)
unnamed: JP1.1 (A), U2.9 (Q)
unnamed: R8.1, U2.8 (~Q), U2.12 (D)
unnamed: R5.2, R7.1, U3.1
unnamed: R4.2, R5.1, U3.3 (+)
unnamed: C1.2, D2.1 (K), R11.1, U3.5 (+)
unnamed: D1.2 (A), U3.7

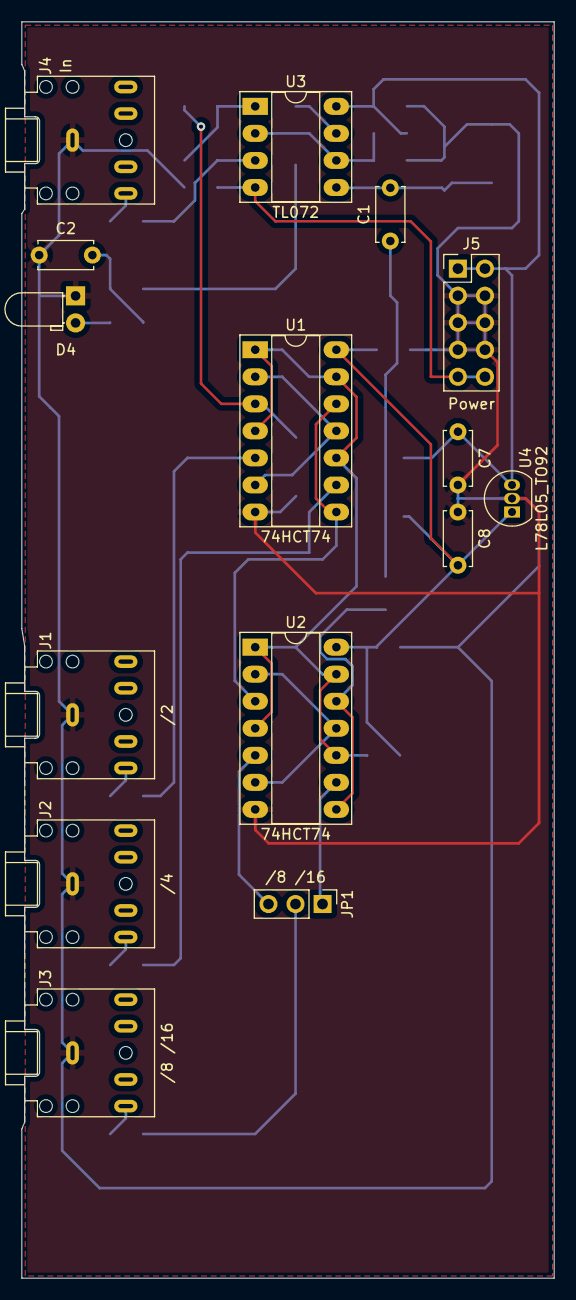
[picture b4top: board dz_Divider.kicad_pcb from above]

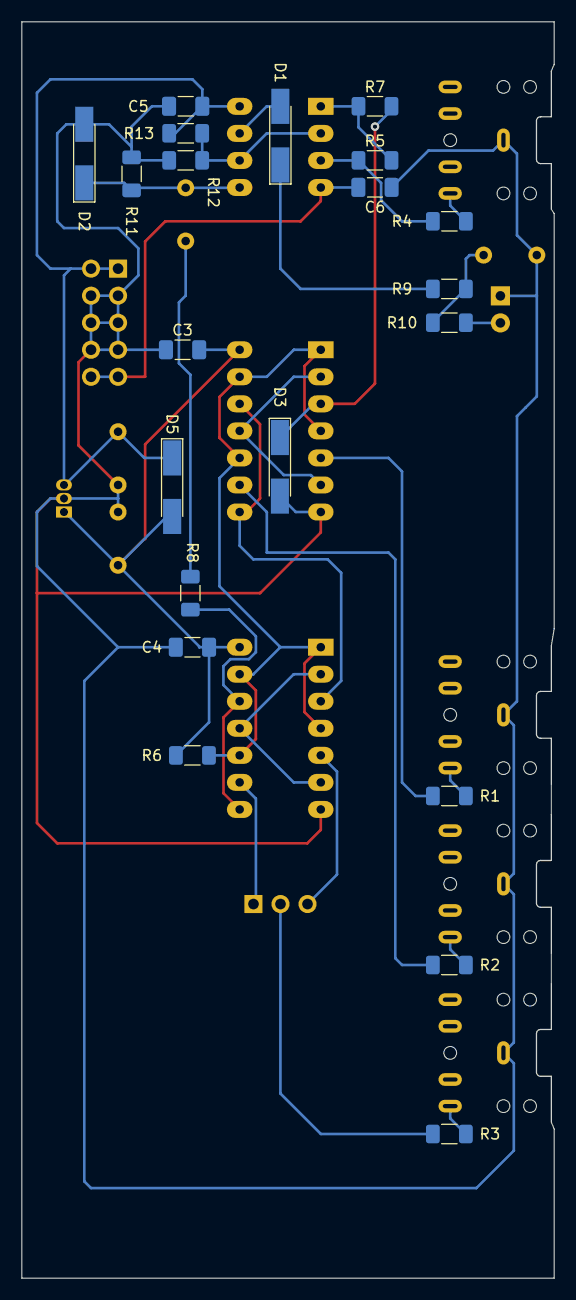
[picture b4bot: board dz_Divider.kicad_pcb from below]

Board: 2 copper layers, 50.0 x 118.0 mm, 36 parts (21 on the bottom side), 28 nets.
